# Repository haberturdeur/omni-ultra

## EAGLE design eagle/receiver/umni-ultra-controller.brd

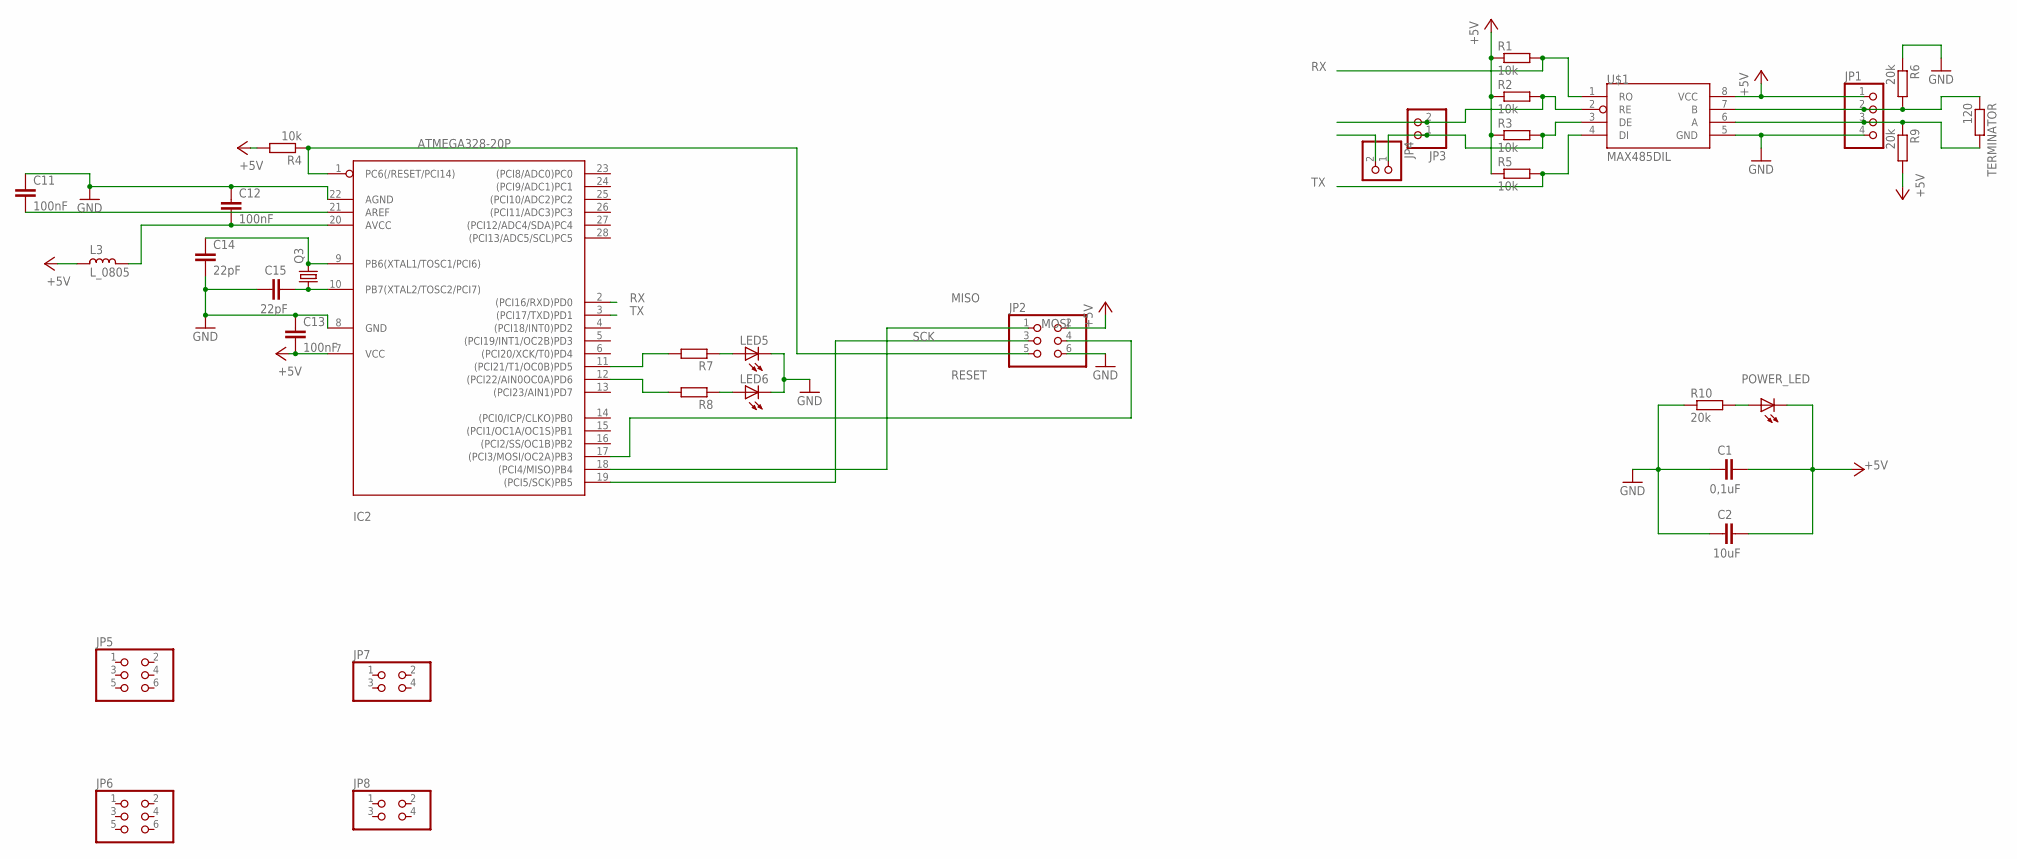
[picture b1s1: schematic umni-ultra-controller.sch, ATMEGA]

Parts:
C1: 0,1uF; C1206
C2: 10uF; C1206
C11, C12, C13: 100nF; C1206
C14, C15: 22pF; C1206
IC2: ATMEGA328-20P; DIL28-3
JP1: PINHD-1X4; 1X04
JP2, JP5, JP6: PINHD-2X3; 2X03
JP3, JP4: PINHD-1X2; 1X02
JP7, JP8: PINHD-2X2; 2X02
L3: L_0805; L0805
LED5, LED6: LED_E; LED_1206
POWER_LED: LED_E; LED_1206
Q3: CRYSTALHC49U-V; HC49U-V
R1, R2, R3, R4, R5: 10k; R1206
R6, R9, R10: 20k; R1206
R7, R8: R-EU_R1206; R1206
TERMINATOR: 120; R1206
U$1: MAX485DIL; DIL08

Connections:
+5V: C1.1, C2.1, C13.2, IC2.7 (VCC), JP1.1, JP2.2, L3.2, POWER_LED.C, R1.1, R2.1, R3.1, R4.2, R5.1, R9.2, U$1.8 (VCC)
GND: C1.2, C2.2, C11.1, C12.1, C13.1, C14.2, C15.2, IC2.8 (GND), IC2.22 (AGND), JP1.4, JP2.6, LED5.C, LED6.C, R6.1, R10.1, U$1.5 (GND)
LED5: IC2.11 ((PCI21/T1/OC0B)PD5), R7.2
LED6: IC2.12 ((PCI22/AIN0OC0A)PD6), R8.2
MISO: IC2.18 ((PCI4/MISO)PB4), JP2.1
MOSI: IC2.17 ((PCI3/MOSI/OC2A)PB3), JP2.4
unnamed: JP1.2, R6.2, TERMINATOR.1, U$1.7 (B)
unnamed: JP1.3, R9.1, TERMINATOR.2, U$1.6 (A)
unnamed: JP3.2, R2.2, U$1.2 (RE)
unnamed: JP3.1, JP4.1, R3.2, U$1.3 (DE)
unnamed: POWER_LED.A, R10.2
unnamed: C11.2, IC2.21 (AREF)
unnamed: C12.2, IC2.20 (AVCC), L3.1
unnamed: LED5.A, R7.1
unnamed: LED6.A, R8.1
unnamed: C14.1, IC2.9 (PB6(XTAL1/TOSC1/PCI6)), Q3.2
unnamed: C15.1, IC2.10 (PB7(XTAL2/TOSC2/PCI7)), Q3.1
RESET: IC2.1 (PC6(/RESET/PCI14)), JP2.5, R4.1
RX: IC2.2 ((PCI16/RXD)PD0), R1.2, U$1.1 (RO)
SCK: IC2.19 ((PCI5/SCK)PB5), JP2.3
TX: IC2.3 ((PCI17/TXD)PD1), R5.2, U$1.4 (DI)

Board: 2 copper layers, 33 parts (0 on the bottom side), 21 nets, no tracks yet.

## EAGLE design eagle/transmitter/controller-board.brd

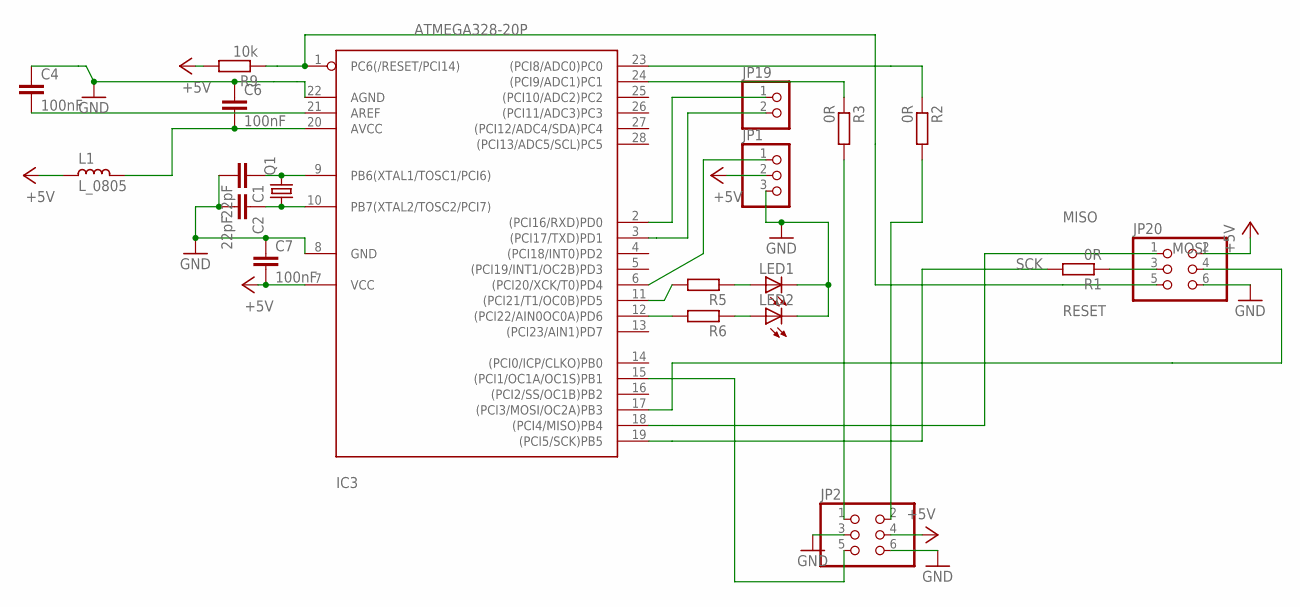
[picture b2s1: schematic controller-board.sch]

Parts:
C1, C2: 22pF; C1206
C4, C6, C7: 100nF; C1206
IC3: ATMEGA328-20P; DIL28-3
JP1: PINHD-1X3; 1X03
JP2, JP20: PINHD-2X3; 2X03
JP19: PINHD-1X2; 1X02
L1: L_0805; L0805
LED1, LED2: LED_E; LED_1206
Q1: CRYSTALHC49U-V; HC49U-V
R1, R2, R3: 0R; R1206
R5, R6: R-EU_R1206; R1206
R9: 10k; R1206

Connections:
+5V: C7.2, IC3.7 (VCC), JP1.2, JP2.4, JP20.2, L1.2, R9.2
GND: C1.2, C2.2, C4.1, C6.1, C7.1, IC3.8 (GND), IC3.22 (AGND), JP1.3, JP2.3, JP2.6, JP20.6, LED1.C, LED2.C
MISO: IC3.18 ((PCI4/MISO)PB4), JP20.1
MOSI: IC3.17 ((PCI3/MOSI/OC2A)PB3), JP20.4
unnamed: IC3.24 ((PCI9/ADC1)PC1), R3.1
unnamed: IC3.23 ((PCI8/ADC0)PC0), R2.1
unnamed: C1.1, IC3.9 (PB6(XTAL1/TOSC1/PCI6)), Q1.2
unnamed: C2.1, IC3.10 (PB7(XTAL2/TOSC2/PCI7)), Q1.1
unnamed: JP20.3, R1.1
unnamed: JP2.2, R2.2
unnamed: JP2.1, R3.2
unnamed: IC3.2 ((PCI16/RXD)PD0), JP19.1
unnamed: IC3.3 ((PCI17/TXD)PD1), JP19.2
unnamed: IC3.11 ((PCI21/T1/OC0B)PD5), R5.2
unnamed: LED1.A, R5.1
unnamed: LED2.A, R6.1
unnamed: IC3.12 ((PCI22/AIN0OC0A)PD6), R6.2
unnamed: IC3.15 ((PCI1/OC1A/OC1S)PB1), JP2.5
unnamed: C4.2, IC3.21 (AREF)
unnamed: C6.2, IC3.20 (AVCC), L1.1
unnamed: IC3.6 ((PCI20/XCK/T0)PD4), JP1.1
RESET: IC3.1 (PC6(/RESET/PCI14)), JP20.5, R9.1
SCK: IC3.19 ((PCI5/SCK)PB5), R1.2

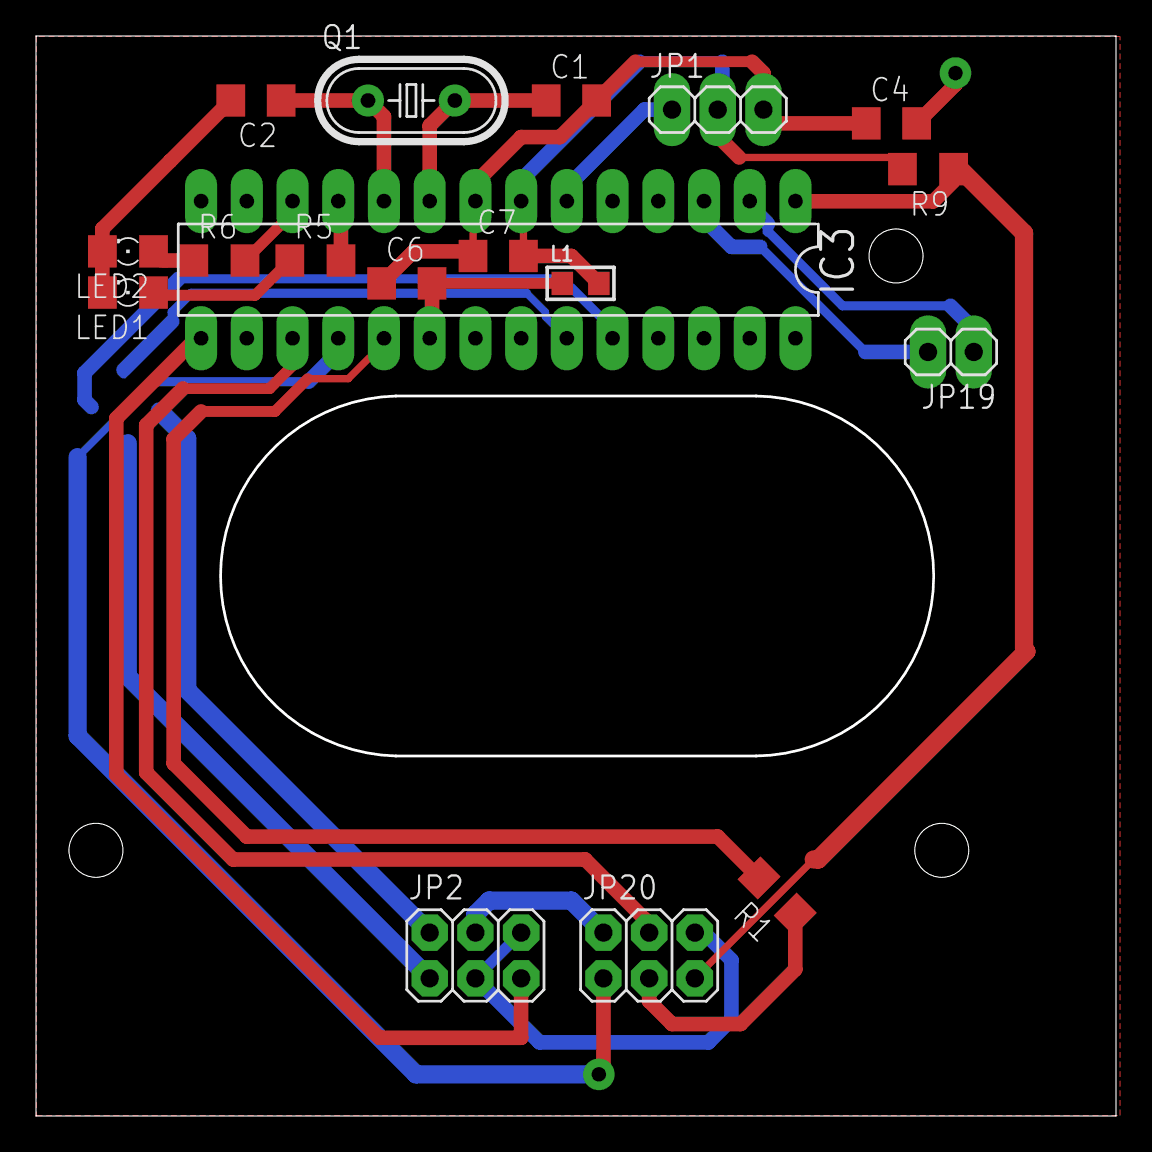
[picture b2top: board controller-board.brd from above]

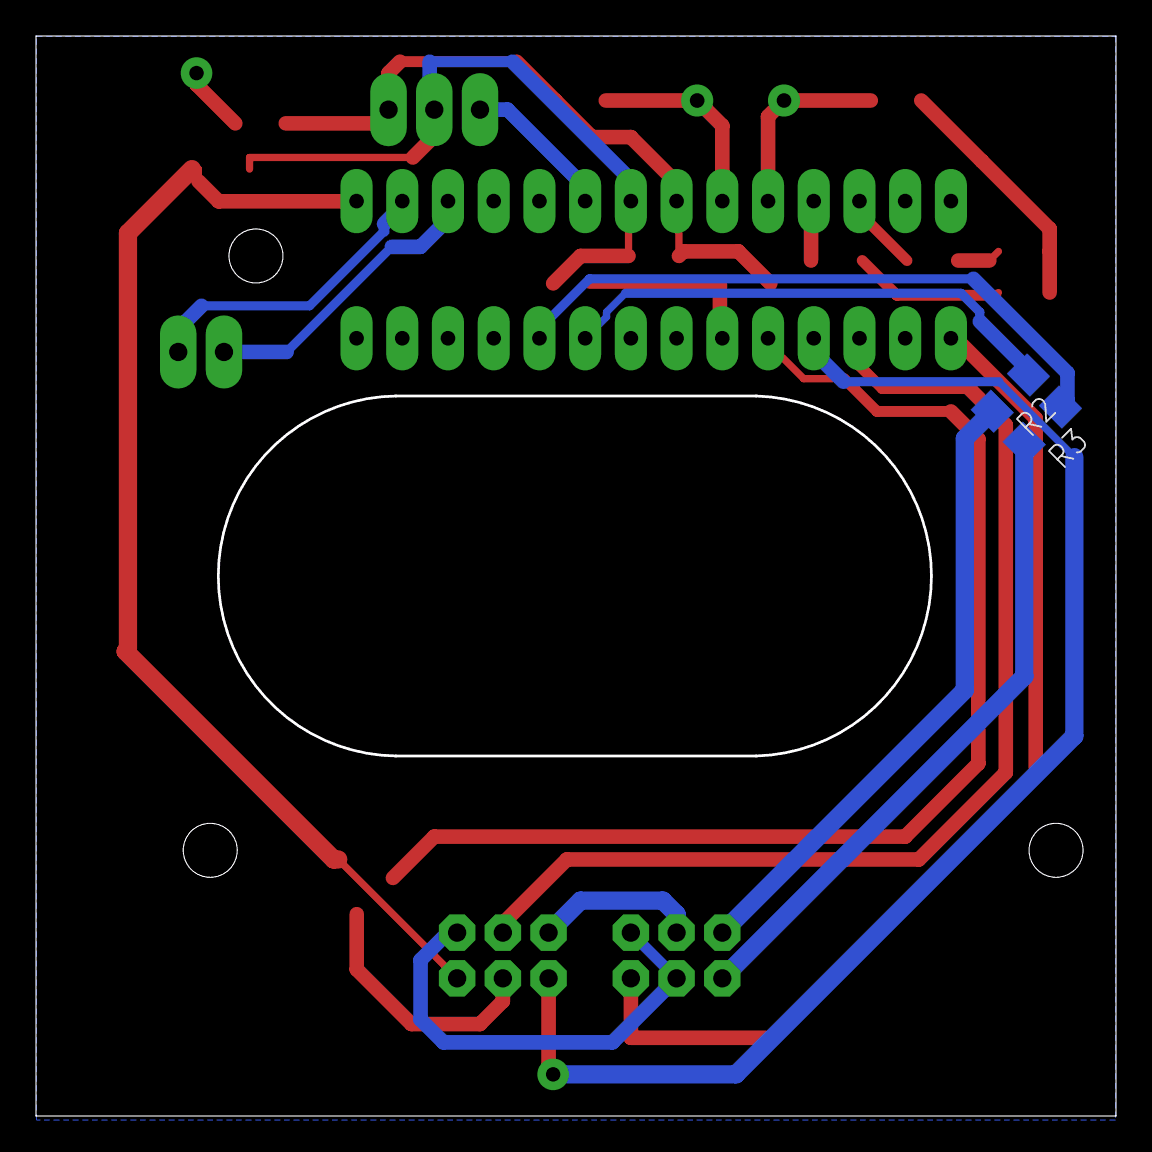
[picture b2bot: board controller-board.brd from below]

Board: 2 copper layers, 59.8 x 59.8 mm, 20 parts (2 on the bottom side), 23 nets.

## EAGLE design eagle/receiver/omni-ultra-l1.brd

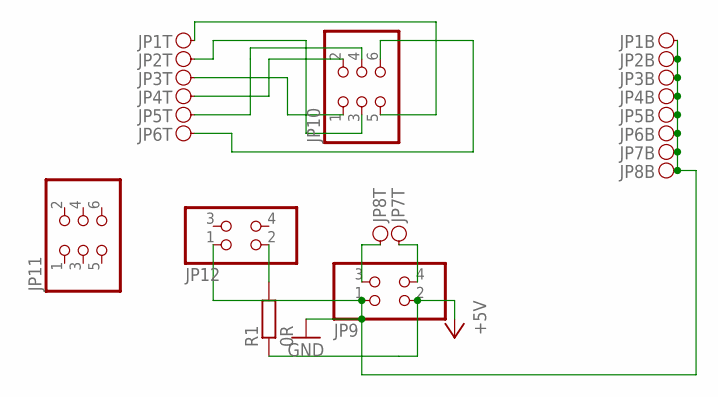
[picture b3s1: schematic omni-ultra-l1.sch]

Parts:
JP1, JP2, JP3, JP4, JP5, JP6, JP7, JP8: PINH2X01; PINH2X01SMD
JP9, JP12: PINHD-2X2; 2X02
JP10, JP11: PINHD-2X3; 2X03
R1: 0R; R1206

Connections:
+5V: JP9.2, R1.1
GND: JP1.B1, JP2.B1, JP3.B1, JP4.B1, JP5.B1, JP6.B1, JP7.B1, JP8.B1, JP9.1, JP12.1
unnamed: JP3.T1, JP10.1
unnamed: JP2.T1, JP10.3
unnamed: JP12.2, R1.2
unnamed: JP4.T1, JP10.2
unnamed: JP5.T1, JP10.4
unnamed: JP6.T1, JP10.6
unnamed: JP8.T1, JP9.3
unnamed: JP7.T1, JP9.4
unnamed: JP1.T1, JP10.5

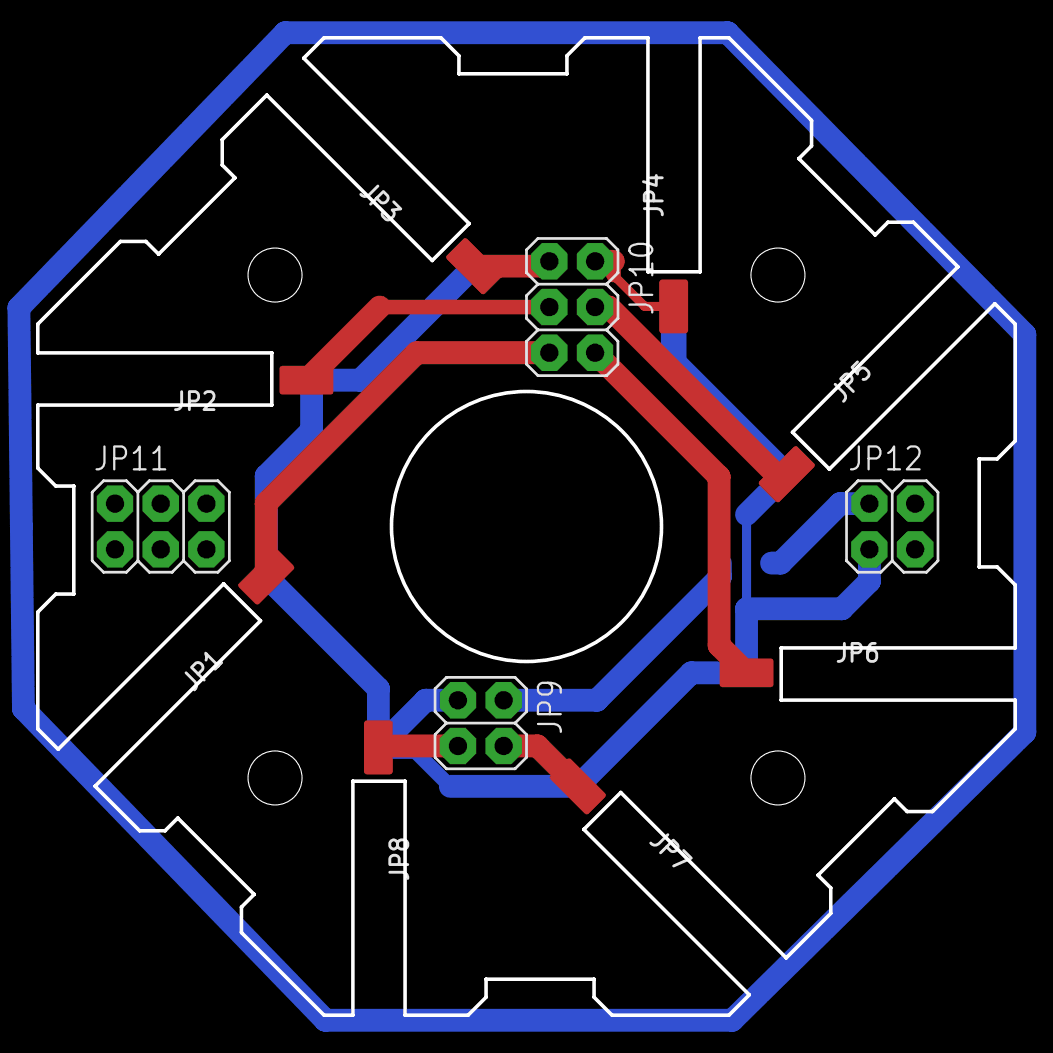
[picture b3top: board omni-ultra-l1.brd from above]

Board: 2 copper layers, 54.3 x 54.3 mm, 13 parts (1 on the bottom side), 11 nets.

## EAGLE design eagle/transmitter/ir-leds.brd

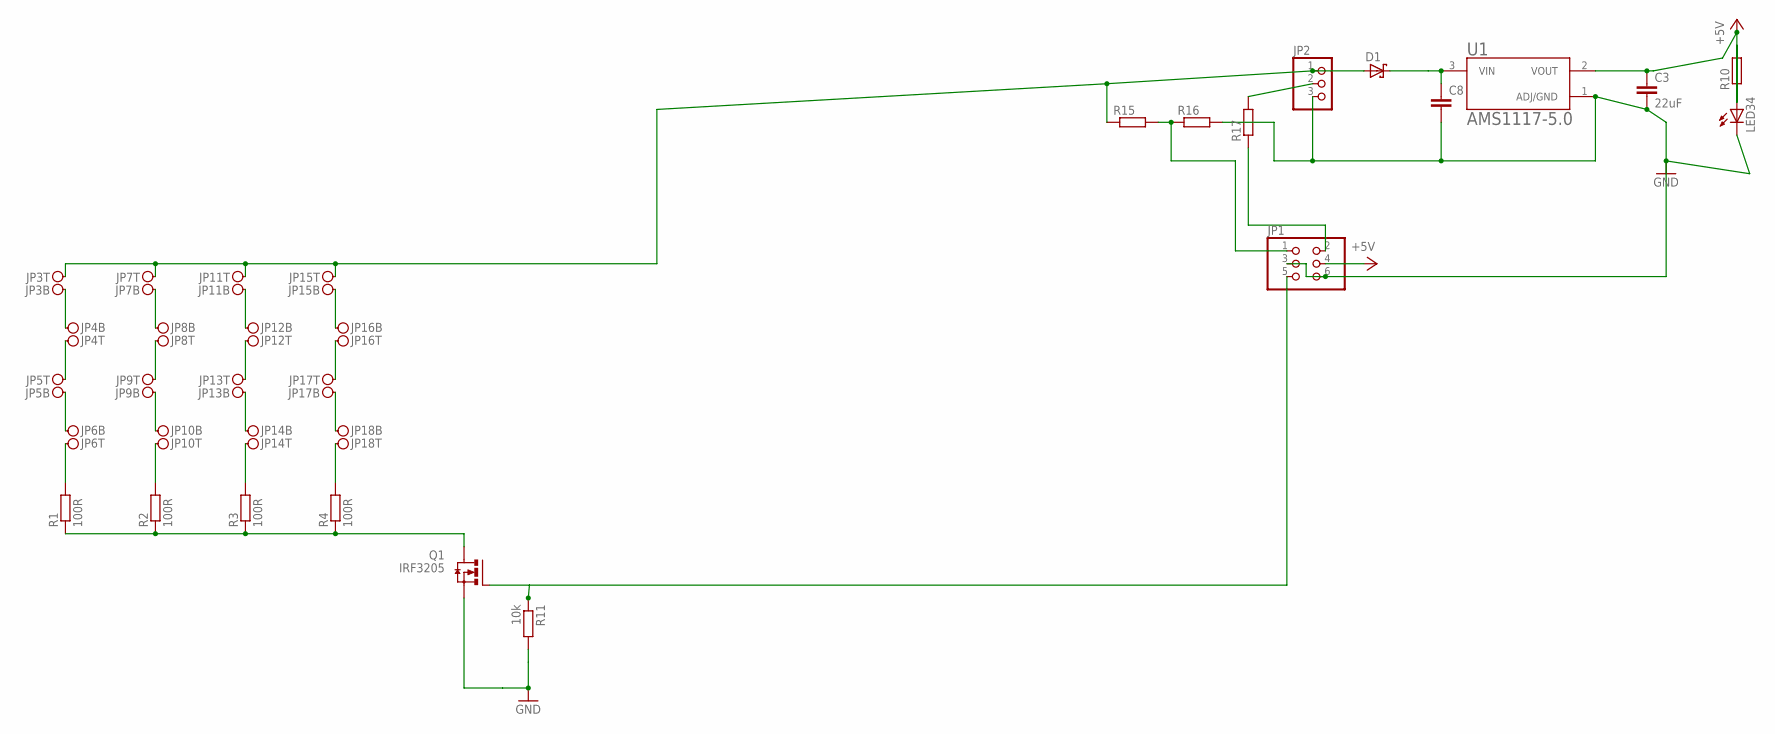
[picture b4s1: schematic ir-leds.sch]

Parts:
C3: 22uF; C1206
C8: CC1206; C1206
D1: SCHOTTKY-DIODEF126Z12; DIODE_F126Z12
JP1: PINHD-2X3; 2X03
JP2: PINHD-1X3; 1X03
JP3, JP4, JP5, JP6, JP7, JP8, JP9, JP10, JP11, JP12, JP13, JP14, JP15, JP16, JP17, JP18: PINH2X01; PINH2X01SMD
LED34: LED_E; LED_1206
Q1: IRF3205; TO262-V
R1, R2, R3, R4: 100R; R1206
R10, R15, R16, R17: R-EU_R1206; R1206
R11: 10k; R1206
U1: AMS1117-5.0; SOT229P700X180-4N

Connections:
+5V: C3.1, JP1.4, R10.2, U1.2 (VOUT)
GND: C3.2, C8.2, JP1.3, JP1.6, JP2.3, LED34.C, Q1.3 (S), R11.2, R16.2, U1.1 (ADJ/GND)
unnamed: JP3.B1, JP4.B1
unnamed: JP4.T1, JP5.T1
unnamed: JP5.B1, JP6.B1
unnamed: JP6.T1, R1.2
unnamed: JP10.T1, R2.2
unnamed: JP9.B1, JP10.B1
unnamed: JP8.T1, JP9.T1
unnamed: JP7.B1, JP8.B1
unnamed: JP11.B1, JP12.B1
unnamed: JP12.T1, JP13.T1
unnamed: JP13.B1, JP14.B1
unnamed: JP14.T1, R3.2
unnamed: JP15.B1, JP16.B1
unnamed: JP16.T1, JP17.T1
unnamed: JP17.B1, JP18.B1
unnamed: JP18.T1, R4.2
unnamed: JP1.2, R17.1
unnamed: D1.A (C), JP2.1, JP3.T1, JP7.T1, JP11.T1, JP15.T1, R15.1
unnamed: JP1.5, Q1.1 (G), R11.1
unnamed: Q1.2 (D), R1.1, R2.1, R3.1, R4.1
unnamed: LED34.A, R10.1
unnamed: JP2.2, R17.2
unnamed: JP1.1, R15.2, R16.1
unnamed: C8.1, D1.C (A), U1.3 (VIN)

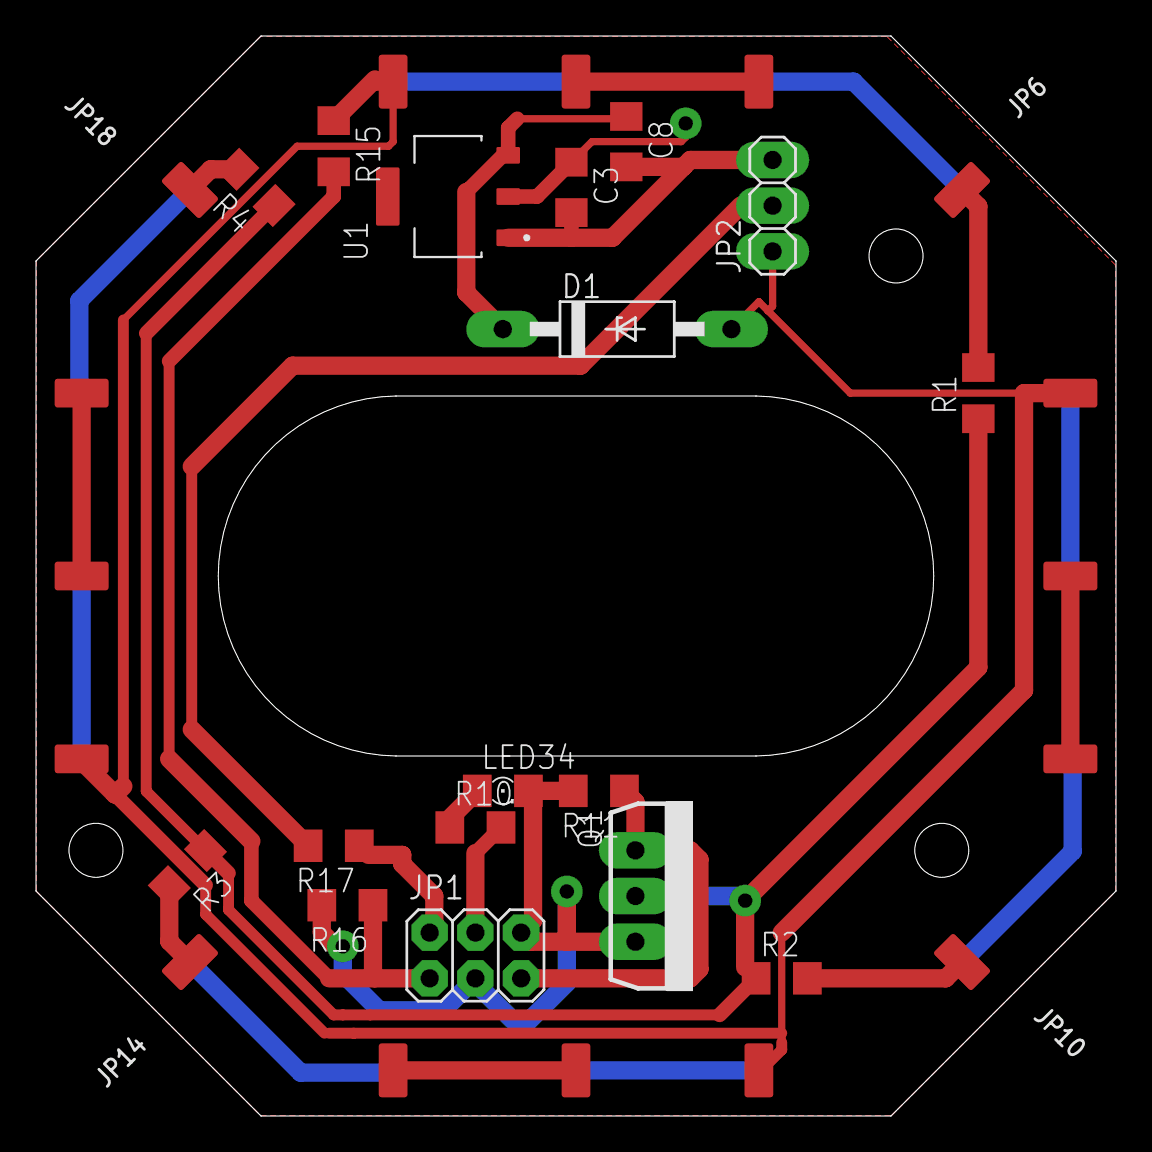
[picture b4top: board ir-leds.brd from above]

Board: 2 copper layers, 60.0 x 60.0 mm, 33 parts (0 on the bottom side), 26 nets.

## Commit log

2019-05-29 init
2019-06-10 added board
2019-06-11 added controler board

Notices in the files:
parts and their libraries:
rc-master-smd: Copyright (C) 2007, Bob Starr
